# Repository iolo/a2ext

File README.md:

# a2ext

Apple II extension-card prototype built around the **WeAct Studio RP2350B Core
Board V1.0**, with interchangeable VGA and DVI daughterboards. It captures the
full 16-bit address bus, shares a main/auxiliary RAM shadow between firmware
backends, and provides UART and an optional active slot-ROM demo.

**Status: implemented schematic and firmware prototypes; hardware acceptance is
open.** Software tests and all three schematic ERC checks pass. Power sequencing,
bus timing, live capture throughput and monitor operation have not been measured.
DVI and the active demo use experimental 252 MHz clocking, above the RP2350
rating. Two-layer through-hole prototype PCB layouts (PCB-P2-THT) and Gerber/drill packages are available;
assembled-board qualification remains open.

## Deliverables

| Component | Files |
|---|---|
| Carrier with direct Apple II bus connections | [KiCad project, PDF, BOM and assembly notes](hw/a2ext-carrier/) |
| RGB333 VGA daughterboard | [KiCad project, PDF, BOM and DAC calculations](hw/a2ext-vga/) |
| DVI over HDMI connector | [KiCad project, PDF, BOM and wiring](hw/a2ext-dvi/) |
| Common capture, API and shadow library | [a2ext-lib](fw/a2ext-lib/README.md) |
| Passive/active demonstration | [a2ext-demo](fw/a2ext-demo/README.md) |

The carrier uses the **99.695 x 78.74 mm compact prototyping-card envelope**;
both daughterboards are 45 x 45 mm. Download the
[carrier Gerbers](hw/a2ext-carrier/a2ext-carrier-gerbers.zip),
[VGA Gerbers](hw/a2ext-vga/a2ext-vga-gerbers.zip), and
[DVI Gerbers](hw/a2ext-dvi/a2ext-dvi-gerbers.zip). Editable boards, layer previews,
and validation reports are alongside each schematic. Read the
[fabrication and assembly notes](hw/PCB-FABRICATION.md) for finishes, connector
selection, socket orientation, and remaining physical tests.
| AppleII-VGA renderer port | [a2ext-vga](fw/a2ext-vga/README.md) |
| A2DVI renderer/libdvi port | [a2ext-dvi](fw/a2ext-dvi/README.md) |

[PRD](PRD.md), [implementation plan](PLAN.md), and [progress record](PROGRESS.md)
describe the scope and per-step commits. [GPIO/IDC assignments](hw/pinout.json)
are the shared hardware/firmware pin contract.

## Build and verify

Use Pico SDK/picotool 2.2.0, ARM GCC/newlib and CMake. The active demo additionally
requires ca65/ld65. See [firmware build instructions](fw/README.md) for dependency
revisions, configuration options and flashing.

```sh
cmake -S . -B build/local -DPICO_SDK_PATH=/path/to/pico-sdk \
  -DPICO_TOOLCHAIN_PATH=/path/to/arm-toolchain -DCMAKE_BUILD_TYPE=Release
cmake --build build/local -j4
python3 tools/smoke.py
python3 tools/smoke.py --erc --firmware-from build/local
```

Builds produce `a2ext-demo`, `a2ext-vga` and `a2ext-dvi` ELF/UF2/map files.
The default demo is passive; video targets render host shadow memory at nominal
640x480/60 Hz. `A2EXT_APPLE_MODEL=IIPLUS` selects II/II+ behavior;
`A2EXT_VIDEO_TEST_PATTERN=ON` selects video test patterns;
`A2EXT_DEMO_ACTIVE=ON` opts into the experimental slot responder.

The [verification record](docs/VERIFICATION.md) separates host replay, clean
builds and ERC from unperformed physical tests. Renderer replay writes images
to `build/replay`. [Resource accounting](docs/resources.md) covers PIO, DMA,
clocking, scheduling and SRAM; no full output framebuffer is allocated.

## Hardware preparation and first use

The module has **two 2x15 headers**, not Pico headers. With all power removed,
prepare its GPIO23 button, GPIO25 LED, secondary-memory branch and USB power path:
remove **R16, R19, R14 when fitted, and on-module U2**; leave U7/R13/C23
unpopulated. U2 removal disables USB power; carrier D2 is omitted. Read the
[carrier assembly notes](hw/a2ext-carrier/README.md) before modifying a module;
on-module designators differ from carrier designators.

All 33 host-bus lines connect directly to GPIO2-34, with an optional SYNC jumper.
GPIO40-47 remain on the 3.3 V daughterboard interface. There is no power-off bus
isolation. Slot pin 25 feeds F1/D1 and the module's **5V (H1.2)** input,
labelled `VSYS` on the carrier; **VBUS (H1.1)** is unconnected. USB is data only.
For flashing, remove the card and supply 5 V through a fixture at slot pins
25/26. Do not hot-plug it. The
[power-transition checks](hw/a2ext-carrier/POWER-VALIDATION.md) and
[bench procedure](docs/HARDWARE-VALIDATION.md) remain open.
Use direct daughterboard mating first. The fused slot rail supplies HDMI +5 V.

UART0 is 115200 8N1, 3.3 V, on IDC pins 1 (TX) and 2 (RX), with ground on 16/20.
Send `?` for passive/video diagnostics. Missing slot-7 SYNC does not gate video.
Capture begins before renderer initialization, but it cannot reconstruct earlier
RAM writes. Unknown bank state requires explicit switch initialization and a host
redraw; warm RESET preserves RAM and reacquires switches. The bench guide gives
a repeatable IIe initialization sequence. Active response limitations, including
late replies and reset races, are documented in the library and demo guides.

## Compatibility scope

| Host/output | Implemented software | Validation |
|---|---|---|
| Apple II / II+ | 40-column normal/inverse/flashing text, lores, hires, mixed, pages 1/2 | Host replay and builds; physical not run |
| Apple IIe | Above plus main/aux banking, 80-column, alternate charset, double lores/hires, 80STORE and IOUDIS | Host replay and builds; physical not run |
| VGA | RGB333, 640x480/60, 126 MHz system clock | Replay/build/ERC; DAC/sync/monitor not run |
| DVI | TMDS via PIO1/PWM, 640x480/60, experimental 252 MHz | Replay/build/ERC; signal/clock/monitor not run |
| Active demo | Slot registers/ROM, C800 ownership, UART, IRQ/NMI | Policy/PIO logic/build; physical timing not run |

US enhanced IIe and US II/II+ fonts are bundled. Unenhanced IIe-specific font,
PAL color emulation, Videx/Video7 interfaces, IIc/IIgs, language-card/RamWorks
shadowing, audio, CEC and EDID negotiation are outside the validated scope.
The two video renderers retain their upstream artifact-color palettes.

## Upstream work

This project adapts [a2pico](https://github.com/oliverschmidt/a2pico),
[AppleII-VGA](https://github.com/markadev/AppleII-VGA) through the
[rallepalaveev fork](https://github.com/rallepalaveev/AppleII-VGA), and
[A2DVI-Firmware](https://github.com/ThorstenBr/A2DVI-Firmware), including libdvi.
Original MIT notices are retained alongside the ports. See
[attribution and revisions](docs/ATTRIBUTION.md). Reference trees are kept
separate from the adapted firmware sources.

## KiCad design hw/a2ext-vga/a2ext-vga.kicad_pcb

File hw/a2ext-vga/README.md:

# a2ext-vga

Revision 0.3 uses A4 landscape with enlarged text: 1.524 mm pin names,
wire labels and values, 1.27 mm pin numbers, and 1.778 mm references/notes.
The revised layout preserves all electrical connections.

KiCad 10 schematic and project-local symbols for a passive 9-bit VGA
daughterboard. J1 follows the common IDC20 pinout. J2 is a female DE-15HD;
its SH pin represents both plated shell/mounting contacts in the selected
project-local DE-15 footprint.

The PCB-P2-THT 45 x 45 mm two-layer board uses axial 1/4 W DIN0207 resistors
with leads formed to 7.62 mm pitch, a bottom-mounted 2x10 female
socket at J1, and a right-angle DE-15HD female connector at J2. The connector
requires 2.29 x 1.90 mm signal pitch, 25 mm shell-hole spacing, and a 3.03 mm
edge-pin-offset pattern. Compare its mechanical drawing before purchasing.
H1/H2 are 2.7 mm spacer holes aligned with the carrier. See
[fabrication notes](../PCB-FABRICATION.md), [Gerbers and drills](a2ext-vga-gerbers.zip),
[top](previews/top.svg), [bottom](previews/bottom.svg), and
[assembly](previews/assembly-top.svg) plots. DRC, ERC, and schematic parity
reports in `validation/` have zero findings.
All components use through-hole leads; no SMD assembly or solder stencil is
required. The original resistor values and tolerances are preserved.

GPIO35-43 are R0-R2, G0-G2, B0-B2. GPIO44/45 are HSYNC/VSYNC. UART, GPIO46/47,
power, and RUN are unused. Both IDC ground contacts connect to VGA grounds and
shell. DDC, ID, and pin 9 power are unconnected, as specified in the PRD.

Each color has 2 kohm, 1 kohm, and 500 ohm resistors for bits 0, 1, and 2.
Use 1% tolerance. With a 75 ohm monitor load and ideal 3.3 V GPIO outputs:

`Vout = 3.3 * (b0/2000 + b1/1000 + b2/500) / (1/75 + 1/2000 + 1/1000 + 1/500)`

The eight nominal levels are 0, 0.0980, 0.1960, 0.2941, 0.3921, 0.4901,
0.5881, and 0.6861 V. Full-scale current is 9.15 mA per color; the MSB GPIO
supplies about 5.23 mA. Firmware pad drive settings must support this load;
start with 8 mA drive and verify voltage and edge quality on hardware. Real
GPIO output impedance changes these ideal values.

R10/R11 are 47 ohm series resistors on sync. Use direct mating to the carrier
for initial qualification; an IDC ribbon cable has no validated length.

Validation: KiCad ERC and exported named-net checks; physical levels and
640x480 timing are not yet tested. Run from the repository root:

```sh
python3 tools/schematics.py vga
python3 tools/check_schematics.py a2ext-vga
```

Design references: PRD resistor network and the bundled A2VGA2 schematic.

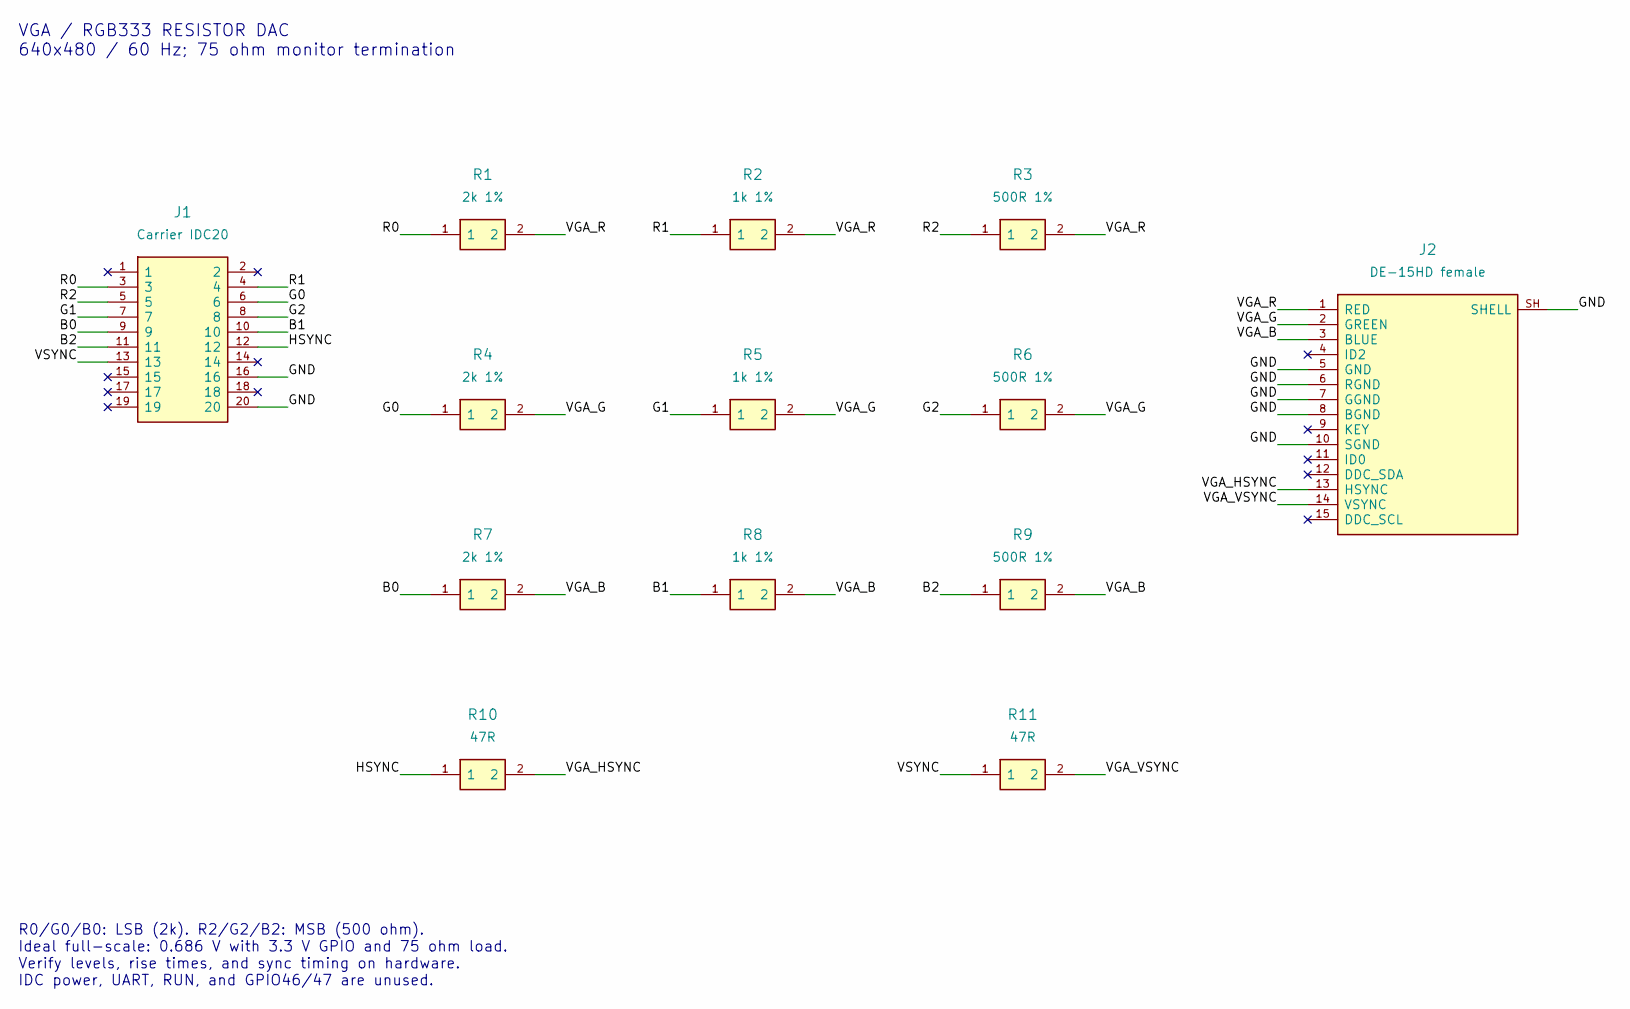
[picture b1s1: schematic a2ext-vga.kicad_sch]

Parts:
J1: Carrier IDC20; Socket20
J2: DE-15HD female; VGA_DE15
R1, R4, R7: 2k 1%; R_Axial_7.62
R2, R5, R8: 1k 1%; R_Axial_7.62
R3, R6, R9: 500R 1%; R_Axial_7.62
R10, R11: 47R; R_Axial_7.62

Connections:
/B0: J1.9, R7.1
/B1: J1.10, R8.1
/B2: J1.11, R9.1
/G0: J1.6, R4.1
/G1: J1.7, R5.1
/G2: J1.8, R6.1
/GND: J1.16, J1.20, J2.5 (GND), J2.6 (RGND), J2.7 (GGND), J2.8 (BGND), J2.10 (SGND), J2.SH (SHELL)
/HSYNC: J1.12, R10.1
/R0: J1.3, R1.1
/R1: J1.4, R2.1
/R2: J1.5, R3.1
/VGA_B: J2.3 (BLUE), R7.2, R8.2, R9.2
/VGA_G: J2.2 (GREEN), R4.2, R5.2, R6.2
/VGA_HSYNC: J2.13 (HSYNC), R10.2
/VGA_R: J2.1 (RED), R1.2, R2.2, R3.2
/VGA_VSYNC: J2.14 (VSYNC), R11.2
/VSYNC: J1.13, R11.1

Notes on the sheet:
VGA / RGB333 RESISTOR DAC 640x480 / 60 Hz; 75 ohm monitor termination
R0/G0/B0: LSB (2k). R2/G2/B2: MSB (500 ohm). Ideal full-scale: 0.686 V with 3.3 V GPIO and 75 ohm load. Verify levels, rise times, and sync timing on hardware. IDC power, UART, RUN, and GPIO46/47 are unused.

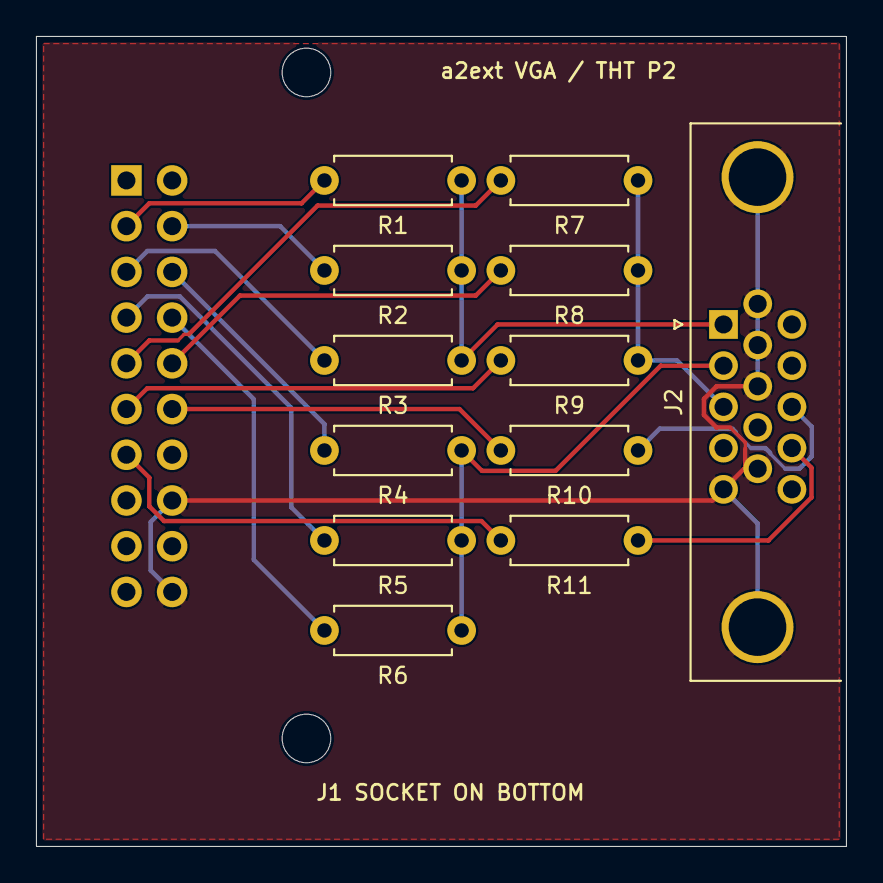
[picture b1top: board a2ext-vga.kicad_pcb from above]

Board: 2 copper layers, 45.0 x 45.0 mm, 15 parts (1 on the bottom side), 17 nets.

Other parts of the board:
H1, H2: MountingHole_2.7mm_M2.5

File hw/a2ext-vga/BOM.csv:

Reference,Value,Footprint,Assembly note
J1,Carrier IDC20,A2Ext:Socket20,Mount female socket on bottom; align pin 1 with carrier J2
J2,DE-15HD female,A2Ext:VGA_DE15,"Right-angle female DE-15HD: 2.29x1.90 mm pins, 25 mm shell holes, 3.03 mm edge offset"
R1,2k 1%,A2Ext:R_Axial_7.62,"Axial DIN0207, 1/4 W, 7.62 mm formed lead pitch; retain stated tolerance"
R2,1k 1%,A2Ext:R_Axial_7.62,"Axial DIN0207, 1/4 W, 7.62 mm formed lead pitch; retain stated tolerance"
R3,500R 1%,A2Ext:R_Axial_7.62,"Axial DIN0207, 1/4 W, 7.62 mm formed lead pitch; retain stated tolerance"
R4,2k 1%,A2Ext:R_Axial_7.62,"Axial DIN0207, 1/4 W, 7.62 mm formed lead pitch; retain stated tolerance"
R5,1k 1%,A2Ext:R_Axial_7.62,"Axial DIN0207, 1/4 W, 7.62 mm formed lead pitch; retain stated tolerance"
R6,500R 1%,A2Ext:R_Axial_7.62,"Axial DIN0207, 1/4 W, 7.62 mm formed lead pitch; retain stated tolerance"
R7,2k 1%,A2Ext:R_Axial_7.62,"Axial DIN0207, 1/4 W, 7.62 mm formed lead pitch; retain stated tolerance"
R8,1k 1%,A2Ext:R_Axial_7.62,"Axial DIN0207, 1/4 W, 7.62 mm formed lead pitch; retain stated tolerance"
R9,500R 1%,A2Ext:R_Axial_7.62,"Axial DIN0207, 1/4 W, 7.62 mm formed lead pitch; retain stated tolerance"
R10,47R,A2Ext:R_Axial_7.62,"Axial DIN0207, 1/4 W, 7.62 mm formed lead pitch; retain stated tolerance"
R11,47R,A2Ext:R_Axial_7.62,"Axial DIN0207, 1/4 W, 7.62 mm formed lead pitch; retain stated tolerance"

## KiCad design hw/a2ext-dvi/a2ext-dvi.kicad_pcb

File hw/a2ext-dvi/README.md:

# a2ext-dvi

Revision 0.3 uses A4 landscape with enlarged text: 1.524 mm pin names,
wire labels and values, 1.27 mm pin numbers, and 1.778 mm references/notes.
The revised layout preserves all electrical connections.

Passive DVI video daughterboard using an HDMI Type A connector and the PRD's
270 ohm series resistor network. Open the KiCad 10 project; symbols are local.
The SH pin represents all four plated shell contacts. The physical PCB selects
**Kycon KDMIX-SL1-NS-WS-B15** for PCB-P2-THT. All 19 signal contacts and four
shell tabs are through-hole. This upright right-angle port exits the right
board edge; its approximately 16.4 mm body height and panel opening require a
new fit check. The PCB-P1 Molex connector cannot fit this revision.

The 45 x 45 mm two-layer board uses axial 1/4 W DIN0207 270 ohm resistors
(7.62 mm formed pitch), a 5.0 mm pitch radial ceramic capacitor,
and a bottom-mounted 2x10 female socket at J1. H1/H2 are 2.7 mm spacer holes
aligned with the carrier. Resistor-to-HDMI pairs use a single layer per pair
without vias: D0/D1 on F.Cu and D2/clock on B.Cu. Output tuning keeps
intra-pair trace-length difference below 0.020 mm. Full routed lengths are in
`validation/summary.json`; the carrier and IDC-to-resistor segments are not
pair-length tuned. Controlled impedance and physical signal quality are unqualified.
See [fabrication notes](../PCB-FABRICATION.md), [Gerbers and drills](a2ext-dvi-gerbers.zip),
[top](previews/top.svg), [bottom](previews/bottom.svg), and
[assembly](previews/assembly-top.svg) plots. DRC, ERC, and schematic parity
reports in `validation/` have zero findings.
No SMD assembly or solder stencil is required. All four shell tabs require
plated slots; retain both drill files when ordering.
`tmds-routing.json` preserves the reviewed pair tracks during regeneration;
the placement generator locks them before routing the other nets.

| Lane | Positive GPIO / IDC | Negative GPIO / IDC | HDMI contacts |
|---|---|---|---|
| D0 | 36 / 4 | 37 / 5 | 7 / 9 |
| D1 | 38 / 6 | 39 / 7 | 4 / 6 |
| D2 | 40 / 8 | 41 / 9 | 1 / 3 |
| Clock | 42 / 10 | 43 / 11 | 10 / 12 |

Each conductor has a 270 ohm, 1% resistor. Shields, pin 17, shell, and both IDC
ground contacts share GND. Pin 18 receives the carrier's fused +5V_DB supply;
there is no additional series diode drop on this board. C1 decouples that rail.
UART, RUN, 3.3 V power, GPIO35/44-47, DDC, HPD, CEC, and utility are unused.

The bundled libdvi program uses the lower GPIO for the positive conductor when
`invert_diffpairs=false`. Use PIO1 base 16 and 64-bit mask helpers. Its clock
generator uses the shared PWM slice for even/odd GPIO42/43. This is the
reference's resistor-driven signaling approach, not a claim of HDMI compliance.

Initially use direct carrier mating. No ribbon cable length is qualified.
Validate a fixed 640x480 timing mode, pair polarity, eye/edge quality, connector
+5 V, and lock on multiple monitors with a real board. No EDID negotiation or
hotplug handling is implemented by this schematic. Carrier power comes from
the slot input (or an off-host fixture at that input); USB is data only.

Validation so far: ERC and named-net export checks. Firmware and physical
TMDS tests are pending. From the repository root:

```sh
python3 tools/schematics.py dvi
python3 tools/check_schematics.py a2ext-dvi
```

References: `ref/A2DVI` v5.x hardware and
`ref/A2DVI-Firmware/libraries/libdvi/dvi_serialiser.{c,pio}`.

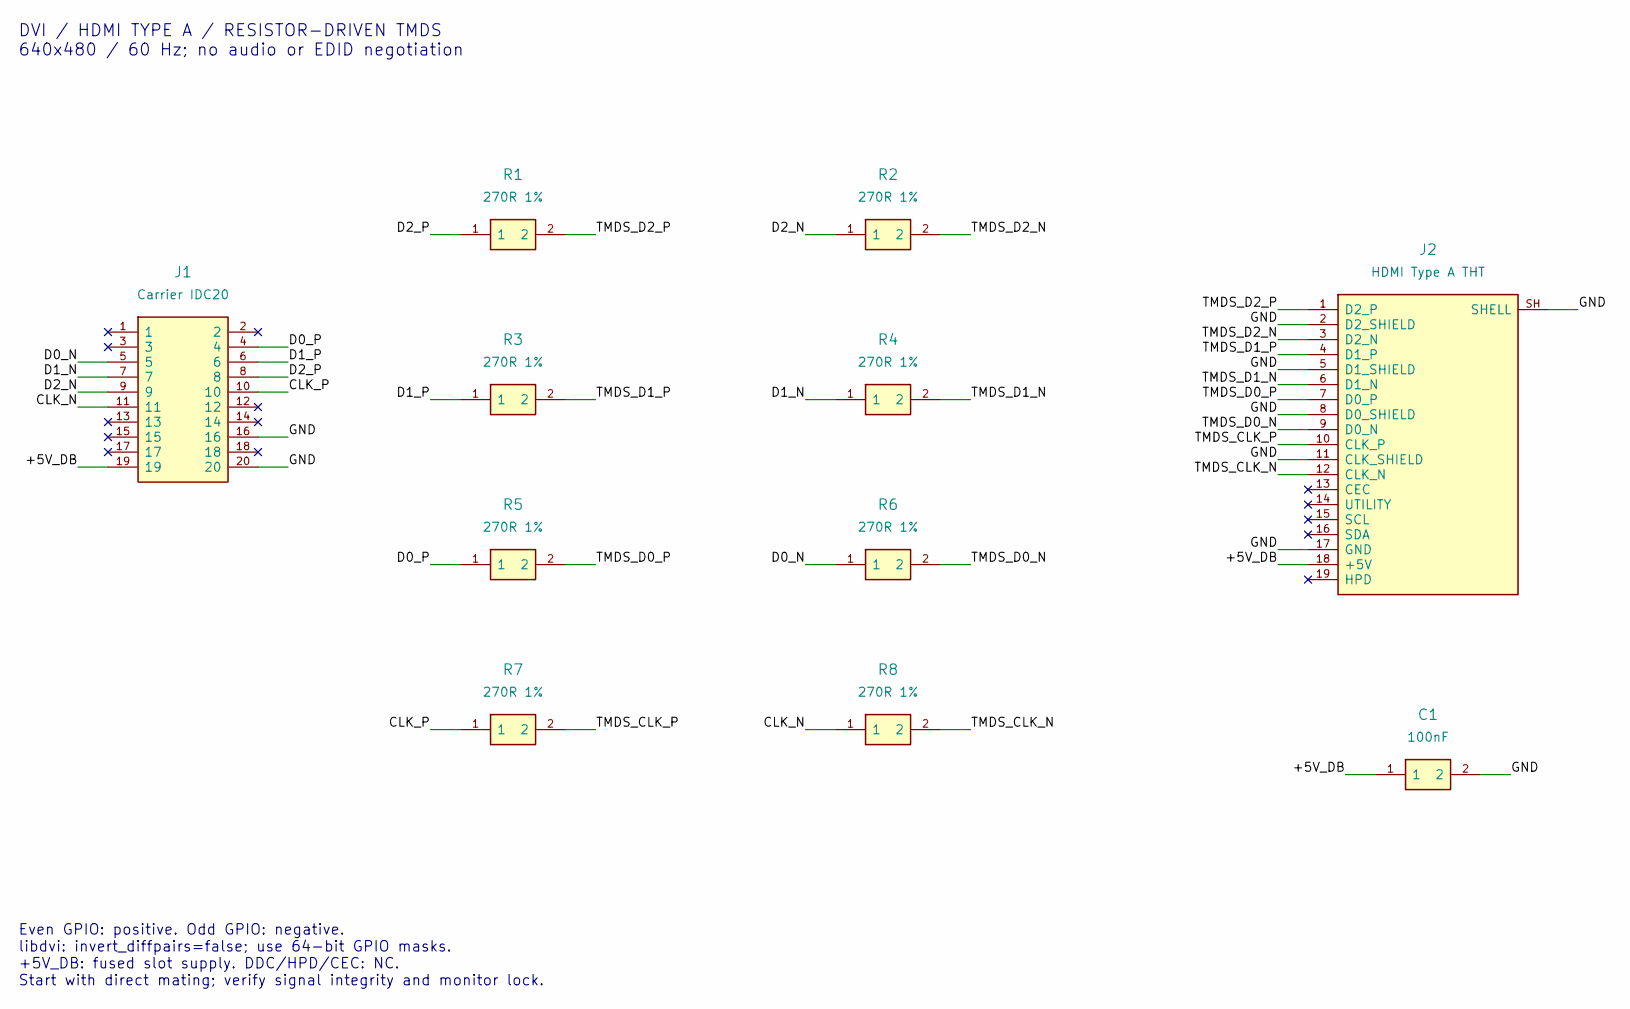
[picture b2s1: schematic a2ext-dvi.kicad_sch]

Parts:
C1: 100nF; C_Radial_5
J1: Carrier IDC20; Socket20
J2: HDMI Type A THT; HDMI_Kycon_THT
R1, R2, R3, R4, R5, R6, R7, R8: 270R 1%; R_Axial_7.62

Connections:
/+5V_DB: C1.1, J1.19, J2.18 (+5V)
/CLK_N: J1.11, R8.1
/CLK_P: J1.10, R7.1
/D0_N: J1.5, R6.1
/D0_P: J1.4, R5.1
/D1_N: J1.7, R4.1
/D1_P: J1.6, R3.1
/D2_N: J1.9, R2.1
/D2_P: J1.8, R1.1
/GND: C1.2, J1.16, J1.20, J2.2 (D2_SHIELD), J2.5 (D1_SHIELD), J2.8 (D0_SHIELD), J2.11 (CLK_SHIELD), J2.17 (GND), J2.SH (SHELL)
/TMDS_CLK_N: J2.12 (CLK_N), R8.2
/TMDS_CLK_P: J2.10 (CLK_P), R7.2
/TMDS_D0_N: J2.9 (D0_N), R6.2
/TMDS_D0_P: J2.7 (D0_P), R5.2
/TMDS_D1_N: J2.6 (D1_N), R4.2
/TMDS_D1_P: J2.4 (D1_P), R3.2
/TMDS_D2_N: J2.3 (D2_N), R2.2
/TMDS_D2_P: J2.1 (D2_P), R1.2

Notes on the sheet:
DVI / HDMI TYPE A / RESISTOR-DRIVEN TMDS 640x480 / 60 Hz; no audio or EDID negotiation
Even GPIO: positive. Odd GPIO: negative. libdvi: invert_diffpairs=false; use 64-bit GPIO masks. +5V_DB: fused slot supply. DDC/HPD/CEC: NC. Start with direct mating; verify signal integrity and monitor lock.

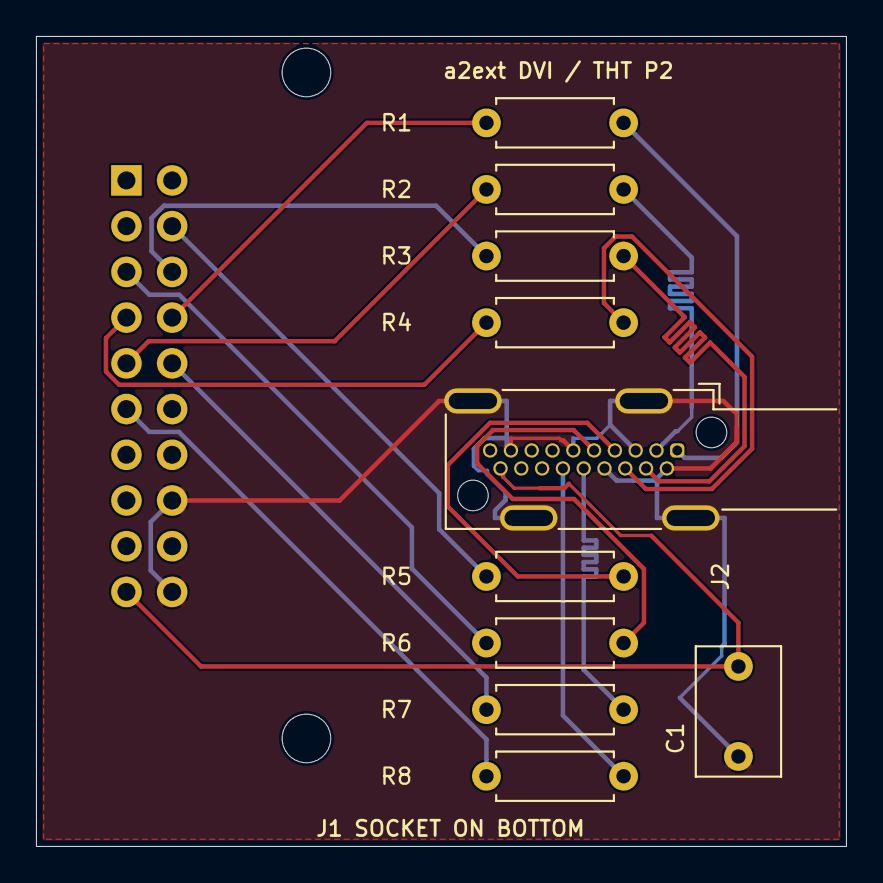
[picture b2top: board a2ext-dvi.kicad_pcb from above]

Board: 2 copper layers, 45.0 x 45.0 mm, 13 parts (1 on the bottom side), 18 nets.

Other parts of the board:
H1, H2: MountingHole_2.7mm_M2.5

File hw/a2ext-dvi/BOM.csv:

Reference,Value,Footprint,Assembly note
J1,Carrier IDC20,A2Ext:Socket20,Mount female socket on bottom; align pin 1 with carrier J2
J2,HDMI Type A THT,A2Ext:HDMI_Kycon_THT,Kycon KDMIX-SL1-NS-WS-B15; all 19 signals and four SH/GND shell contacts through-hole
R1,270R 1%,A2Ext:R_Axial_7.62,"Axial DIN0207, 1/4 W, 7.62 mm formed lead pitch; retain stated tolerance"
R2,270R 1%,A2Ext:R_Axial_7.62,"Axial DIN0207, 1/4 W, 7.62 mm formed lead pitch; retain stated tolerance"
R3,270R 1%,A2Ext:R_Axial_7.62,"Axial DIN0207, 1/4 W, 7.62 mm formed lead pitch; retain stated tolerance"
R4,270R 1%,A2Ext:R_Axial_7.62,"Axial DIN0207, 1/4 W, 7.62 mm formed lead pitch; retain stated tolerance"
R5,270R 1%,A2Ext:R_Axial_7.62,"Axial DIN0207, 1/4 W, 7.62 mm formed lead pitch; retain stated tolerance"
R6,270R 1%,A2Ext:R_Axial_7.62,"Axial DIN0207, 1/4 W, 7.62 mm formed lead pitch; retain stated tolerance"
R7,270R 1%,A2Ext:R_Axial_7.62,"Axial DIN0207, 1/4 W, 7.62 mm formed lead pitch; retain stated tolerance"
R8,270R 1%,A2Ext:R_Axial_7.62,"Axial DIN0207, 1/4 W, 7.62 mm formed lead pitch; retain stated tolerance"
C1,100nF,A2Ext:C_Radial_5,"100nF radial ceramic, >=10V; 5.0 mm lead pitch; nonpolar; <=7.0x4.5 mm body"

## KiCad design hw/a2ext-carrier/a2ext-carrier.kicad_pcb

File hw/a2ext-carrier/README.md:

# a2ext-carrier schematic prototype

Open `a2ext-carrier.kicad_pro` in KiCad 10. Symbols are project-local and embedded
in the schematic. `BOM.csv` lists component values and assigned physical
footprints, retained during schematic regeneration. `connections.json` is the
generated connectivity contract, checked against KiCad's exported netlist.

Revision 0.6 uses A4 landscape with 1.524 mm pin names, wire labels, and values;
pin numbers are 1.27 mm and references/notes are 1.778 mm. Symbols and notes
are rearranged for printing at actual size; electrical connections are unchanged.
PCB-P2-THT uses axial resistors, a 1N5819 DO-41 diode, Bourns MF-R050/MF-R010
radial resettable fuses and nonpolar leaded ceramic capacitors. All component
leads on the carrier are through-hole; M1 is still a preassembled SMD module
plugged into sockets. There are no separate DIP ICs in the schematic.

**Status: schematic draft, not electrically qualified.** ERC checks connectivity,
not bus timing, power sequencing, module thermals, or Apple II compatibility.

The two-layer prototype board uses the Tebl compact envelope: 99.695 x 78.74 mm
including the insertion tab. The 60-pad module footprint follows the vendor top
view; use two 2x15 female sockets. J2 is a top-mounted shrouded male IDC20 header.
H1/H2 are 2.7 mm daughterboard spacer holes; their references differ from module
headers. See [Gerbers and drills](a2ext-carrier-gerbers.zip),
[top](previews/top.svg), [bottom](previews/bottom.svg),
[assembly](previews/assembly-top.svg), and [fabrication notes](../PCB-FABRICATION.md).
DRC, ERC, and schematic parity reports in `validation/` have zero findings.

## Module and connections

M1 represents both WeAct V1.0 headers. Pin numbers `H1.n` and `H2.n` refer to
the vendor schematic, not arbitrary carrier header numbering. Do not substitute
a Pico 2 or Clintech module. See the module drawing for orientation.

Prepare the module with power disconnected: remove R16 (KEY/GPIO23), R19
(LED/GPIO25), R14 (secondary chip select), and **on-module U2** (the vendor's
unidentified VBUS-to-5V power-path device). Leave secondary memory U7/R13/C23
unpopulated. Removing U2 disconnects USB VBUS from the module supply; do not
bridge its vacated input/output pads. Carrier D2 is removed and M1 H1.1 (VBUS)
is unconnected. Inspect and continuity-test these modifications. USB is for
data only and cannot power the prepared card.

J1 follows the PRD's counter-clockwise slot numbering. /INT and /DMA chains
pass through. Unused negative supplies, +12V, /RDY, /DMA, /INH, and auxiliary
clocks are not connected. JP1 defaults open: close it only when motherboard
documentation confirms composite SYNC on slot 7 pin 19. UART0 and all 13 general
daughterboard GPIOs are on J2. /RES is sensed separately from module RUN.

## Direct bus and power

Revision 0.5 retains direct connections for all 33 bus signals to GPIO2-34,
with JP1 in the optional SYNC path. Wire labels use Apple II signal names
(`A0`, `D0`, `IOSEL_N`, etc.), `UART_TX`/`UART_RX`, and daughterboard names
such as `IDC03_GPIO35`. `_N` means active low; UART direction is from the
carrier's perspective. M1 shows the physical GPIO names and WeAct header
contacts; J2 shows pin functions alongside its contact numbers. Matching
wire labels identify the same electrical net. No bus switches, supervisors,
or BUS_GOOD/BUS_OE_N control circuit remain. GPIO40-47 stay on the 3.3 V
daughterboard interface. Firmware
must drive IRQ/NMI low or release them; the host supplies their pull-ups.

RP2350 fault-tolerant digital inputs support 5 V with IOVDD powered at 3.3 V.
The direct connection provides no protection against a live 5 V bus with an
unpowered module. All operating power comes from the slot supply. Flash with
the card removed from the host, using a 5 V fixture at J1 pins 25/26 and USB
for data only; do not hot-plug the card. Measure startup/shutdown
and brownout behavior using the [power-validation procedure](POWER-VALIDATION.md).

R4 retains the module RUN pull-up. RUN resets M1 but does not disconnect bus
pins; Apple /RES remains a separate input.

The power path is `J1.25 (+5V_SLOT) -> F1 -> D1 -> VSYS -> M1 H1.2`.
The WeAct module labels H1.2 **5V**; it feeds the regulator input and serves the
same function as Pico's VSYS. H1.1 is **VBUS**, and stays unconnected on the
carrier. D1 is retained as reverse-current protection, with its anode toward
F1 and cathode toward VSYS. C9 decouples VSYS. F2 feeds +5V_DB from the fused
slot rail before D1. J2 power pins are outputs, not auxiliary inputs.

Initial allocation: at most 400 mA for carrier/module plus 100 mA for the
daughterboard from the slot branch, subject to the actual host's available
budget and PTC derating. This is a design ceiling, not a measured consumption
or a fuse trip-current guarantee. The module regulator's part number/current
rating is unspecified in the vendor drawing; reserve the 3.3 V daughterboard
pin for light loads until that rating and module temperature are established.

## Checks and outstanding work

```sh
python3 tools/pinout.py
python3 tools/check_schematics.py a2ext-carrier
```

Run from the repository root. Regenerate explicitly with
`python3 tools/schematics.py carrier`; review changes before replacing manual
edits. Export the PDF with `kicad-cli sch export pdf`.

Physical release requires power-transition, supply/thermal, and bus timing
measurements. ERC does not establish the WeAct module's supply ramp behavior.

Sources: vendor module files in `ref/WeActStudio.RP2350BCoreBoard/HDK/`,
[RP2350 datasheet](https://datasheets.raspberrypi.com/rp2350/rp2350-datasheet.pdf).

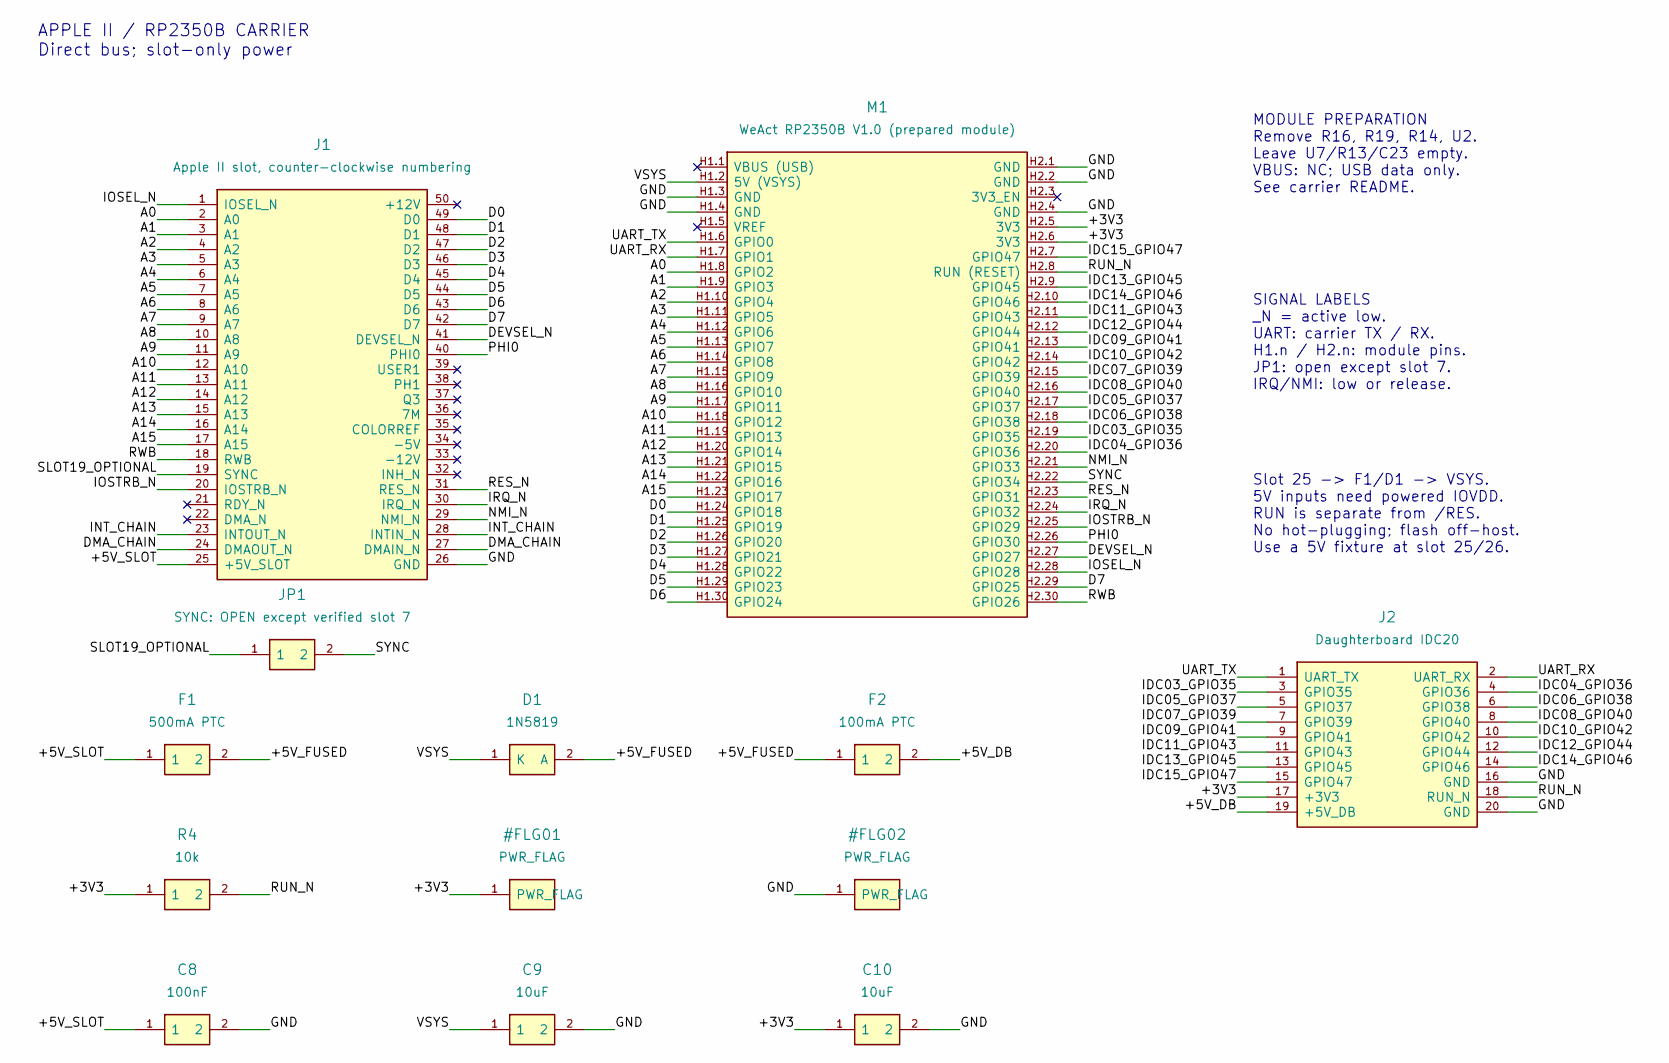
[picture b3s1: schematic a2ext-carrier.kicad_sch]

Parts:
C8: 100nF; C_Radial_5
C9, C10: 10uF; C_Radial_5
D1: 1N5819; Schottky_DO41
F1: 500mA PTC; PTC_MF_R050
F2: 100mA PTC; PTC_MF_R010
J1: Apple II slot, counter-clockwise numbering; AppleII_Edge50
J2: Daughterboard IDC20; IDC20
JP1: SYNC: OPEN except verified slot 7; SYNC
M1: WeAct RP2350B V1.0 (prepared module); WeAct_RP2350B_V1
R4: 10k; R_Axial_7.62

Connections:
/+3V3: C10.1, J2.17 (+3V3), M1.H2.5 (3V3), M1.H2.6 (3V3), R4.1
/+5V_DB: F2.2, J2.19 (+5V_DB)
/+5V_FUSED: D1.2 (A), F1.2, F2.1
/+5V_SLOT: C8.1, F1.1, J1.25 (+5V_SLOT)
/A0: J1.2 (A0), M1.H1.8 (GPIO2)
/A1: J1.3 (A1), M1.H1.9 (GPIO3)
/A2: J1.4 (A2), M1.H1.10 (GPIO4)
/A3: J1.5 (A3), M1.H1.11 (GPIO5)
/A4: J1.6 (A4), M1.H1.12 (GPIO6)
/A5: J1.7 (A5), M1.H1.13 (GPIO7)
/A6: J1.8 (A6), M1.H1.14 (GPIO8)
/A7: J1.9 (A7), M1.H1.15 (GPIO9)
/A8: J1.10 (A8), M1.H1.16 (GPIO10)
/A9: J1.11 (A9), M1.H1.17 (GPIO11)
/A10: J1.12 (A10), M1.H1.18 (GPIO12)
/A11: J1.13 (A11), M1.H1.19 (GPIO13)
/A12: J1.14 (A12), M1.H1.20 (GPIO14)
/A13: J1.15 (A13), M1.H1.21 (GPIO15)
/A14: J1.16 (A14), M1.H1.22 (GPIO16)
/A15: J1.17 (A15), M1.H1.23 (GPIO17)
/D0: J1.49 (D0), M1.H1.24 (GPIO18)
/D1: J1.48 (D1), M1.H1.25 (GPIO19)
/D2: J1.47 (D2), M1.H1.26 (GPIO20)
/D3: J1.46 (D3), M1.H1.27 (GPIO21)
/D4: J1.45 (D4), M1.H1.28 (GPIO22)
/D5: J1.44 (D5), M1.H1.29 (GPIO23)
/D6: J1.43 (D6), M1.H1.30 (GPIO24)
/D7: J1.42 (D7), M1.H2.29 (GPIO25)
/DEVSEL_N: J1.41 (DEVSEL_N), M1.H2.27 (GPIO27)
/DMA_CHAIN: J1.24 (DMAOUT_N), J1.27 (DMAIN_N)
/GND: C8.2, C9.2, C10.2, J1.26 (GND), J2.16 (GND), J2.20 (GND), M1.H1.3 (GND), M1.H1.4 (GND), M1.H2.1 (GND), M1.H2.2 (GND), M1.H2.4 (GND)
/IDC03_GPIO35: J2.3 (GPIO35), M1.H2.19 (GPIO35)
/IDC04_GPIO36: J2.4 (GPIO36), M1.H2.20 (GPIO36)
/IDC05_GPIO37: J2.5 (GPIO37), M1.H2.17 (GPIO37)
/IDC06_GPIO38: J2.6 (GPIO38), M1.H2.18 (GPIO38)
/IDC07_GPIO39: J2.7 (GPIO39), M1.H2.15 (GPIO39)
/IDC08_GPIO40: J2.8 (GPIO40), M1.H2.16 (GPIO40)
/IDC09_GPIO41: J2.9 (GPIO41), M1.H2.13 (GPIO41)
/IDC10_GPIO42: J2.10 (GPIO42), M1.H2.14 (GPIO42)
/IDC11_GPIO43: J2.11 (GPIO43), M1.H2.11 (GPIO43)
/IDC12_GPIO44: J2.12 (GPIO44), M1.H2.12 (GPIO44)
/IDC13_GPIO45: J2.13 (GPIO45), M1.H2.9 (GPIO45)
/IDC14_GPIO46: J2.14 (GPIO46), M1.H2.10 (GPIO46)
/IDC15_GPIO47: J2.15 (GPIO47), M1.H2.7 (GPIO47)
/INT_CHAIN: J1.23 (INTOUT_N), J1.28 (INTIN_N)
/IOSEL_N: J1.1 (IOSEL_N), M1.H2.28 (GPIO28)
/IOSTRB_N: J1.20 (IOSTRB_N), M1.H2.25 (GPIO29)
/IRQ_N: J1.30 (IRQ_N), M1.H2.24 (GPIO32)
/NMI_N: J1.29 (NMI_N), M1.H2.21 (GPIO33)
/PHI0: J1.40 (PHI0), M1.H2.26 (GPIO30)
/RES_N: J1.31 (RES_N), M1.H2.23 (GPIO31)
/RUN_N: J2.18 (RUN_N), M1.H2.8 (RUN (RESET)), R4.2
/RWB: J1.18 (RWB), M1.H2.30 (GPIO26)
/SLOT19_OPTIONAL: J1.19 (SYNC), JP1.1
/SYNC: JP1.2, M1.H2.22 (GPIO34)
/UART_RX: J2.2 (UART_RX), M1.H1.7 (GPIO1)
/UART_TX: J2.1 (UART_TX), M1.H1.6 (GPIO0)
/VSYS: C9.1, D1.1 (K), M1.H1.2 (5V (VSYS))

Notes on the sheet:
APPLE II / RP2350B CARRIER Direct bus; slot-only power
MODULE PREPARATION Remove R16, R19, R14, U2. Leave U7/R13/C23 empty. VBUS: NC; USB data only. See carrier README.
SIGNAL LABELS _N = active low. UART: carrier TX / RX. H1.n / H2.n: module pins. JP1: open except slot 7. IRQ/NMI: low or release.
Slot 25 -> F1/D1 -> VSYS. 5V inputs need powered IOVDD. RUN is separate from /RES. No hot-plugging; flash off-host. Use a 5V fixture at slot 25/26.

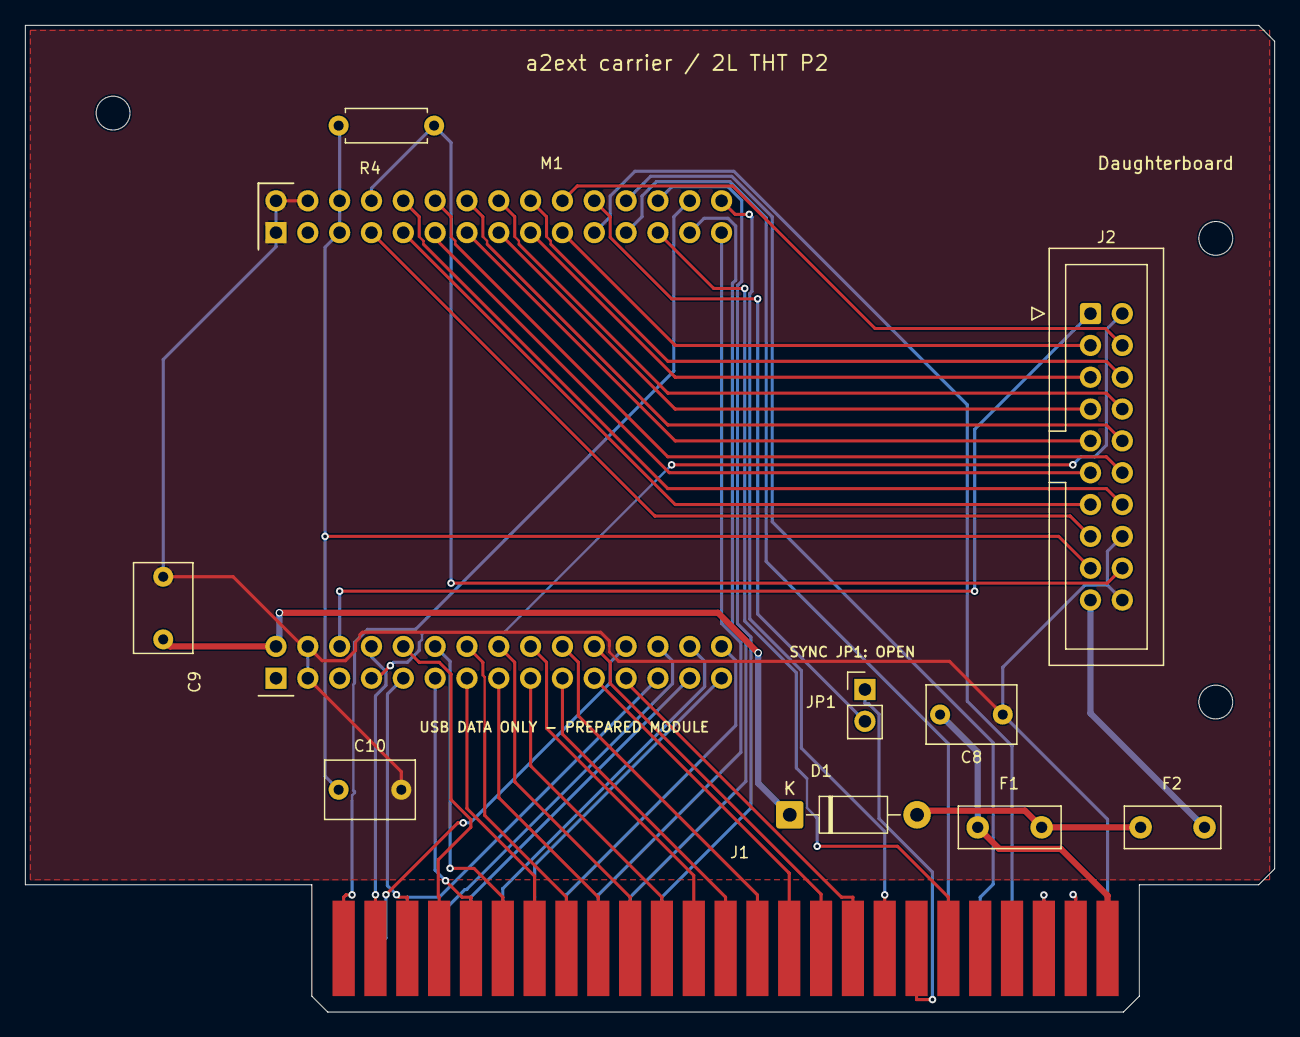
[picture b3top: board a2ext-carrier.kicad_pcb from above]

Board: 2 copper layers, 99.7 x 78.7 mm, 14 parts (0 on the bottom side), 58 nets.

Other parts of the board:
H1, H2, H3: MountingHole_2.7mm_M2.5

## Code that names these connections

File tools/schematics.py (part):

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    nets["19"] = "SLOT19_OPTIONAL"
    b.part("J1", "AppleII_Slot", "Apple II slot, counter-clockwise numbering", 60.96, 73.66, nets)
    b.two("JP1", "SYNC: OPEN except verified slot 7", "SLOT19_OPTIONAL", bus_nets[19], 55.88, 119.38, "Jumper")
    h1 = {1:"VBUS",2:"5V",3:"GND",4:"GND",5:"VREF",6:"GPIO0"}
    h1.update({i+6:f"GPIO{i}" for i in range(1,25)})
    h2 = {1:"GND",2:"GND",3:"3V3_EN",4:"GND",5:"3V3",6:"3V3",7:"GPIO47",8:"RUN"}
    h2.update({i:f"GPIO{56-i}" for i in range(9,31)})
    # H2 rows after RUN: odd contacts descend 47,45,...25; even descend 46,...26.
    h2.update({i:f"GPIO{54-i}" for i in range(9,31,2)})
    h2.update({i:f"GPIO{56-i}" for i in range(10,31,2)})
    power_labels = {"5V": "5V (VSYS)", "VBUS": "VBUS (USB)", "RUN": "RUN (RESET)"}
    b.symbol("WeAct_RP2350B_V1", [(f"H1.{i}",power_labels.get(h1[i],h1[i]),"passive") for i in range(1,31)],
             [(f"H2.{i}",power_labels.get(h2[i],h2[i]),"passive") for i in range(1,31)], 50.8)
    module = {}
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    b.two("R10","47R","HSYNC","VGA_HSYNC",91.44,139.7)
    b.two("R11","47R","VSYNC","VGA_VSYNC",182.88,139.7)
    b.text("VGA / RGB333 RESISTOR DAC\n640x480 / 60 Hz; 75 ohm monitor termination",12.7,12.7,2.032)
    b.text("R0/G0/B0: LSB (2k). R2/G2/B2: MSB (500 ohm).\nIdeal full-scale: 0.686 V with 3.3 V GPIO and 75 ohm load.\nVerify levels, rise times, and sync timing on hardware.\nIDC power, UART, RUN, and GPIO46/47 are unused.",12.7,165.1)
    b.save()


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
